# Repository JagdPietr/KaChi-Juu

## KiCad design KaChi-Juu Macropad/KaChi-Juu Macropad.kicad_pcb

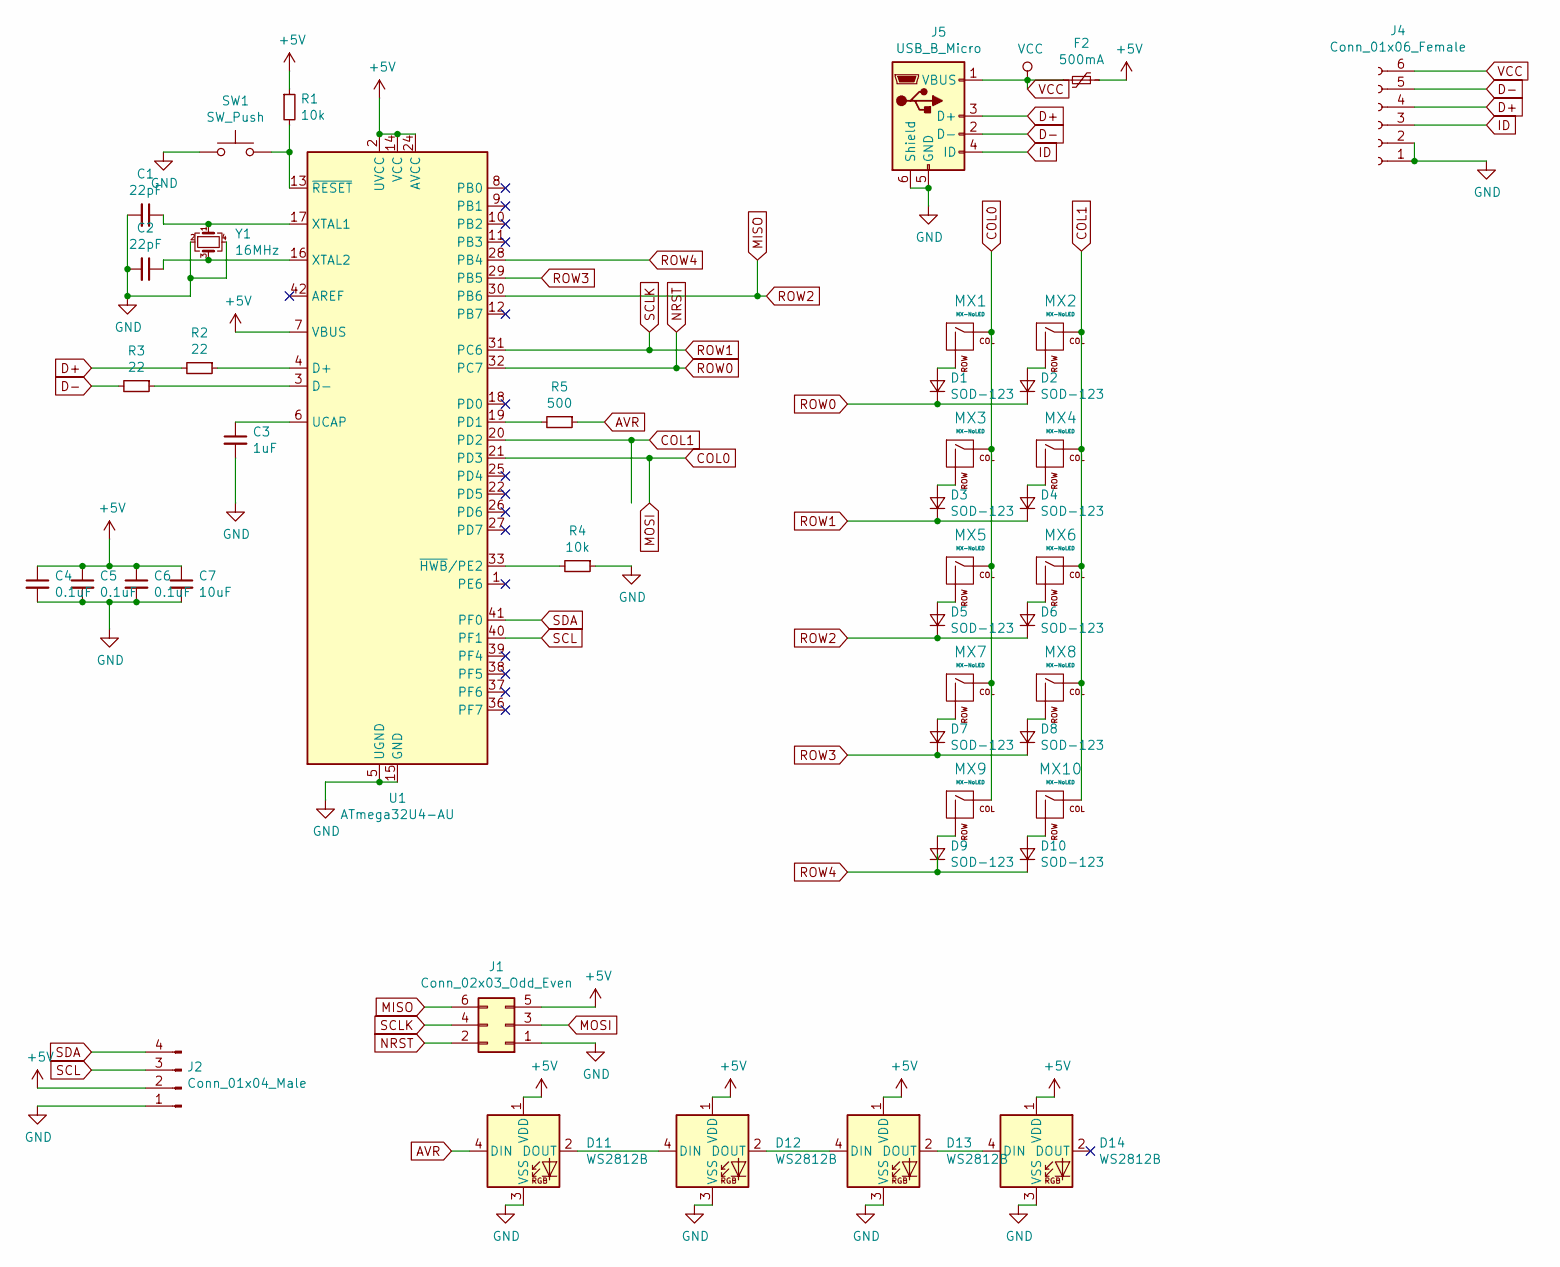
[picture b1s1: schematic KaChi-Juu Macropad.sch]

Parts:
C1, C2: 22pF; C_0805_2012Metric
C3: 1uF; C_0805_2012Metric
C4, C5, C6: 0.1uF; C_0805_2012Metric
C7: 10uF; C_0805_2012Metric
D1, D2, D3, D4, D5, D6, D7, D8, D9, D10: SOD-123; D_SOD-123
D11, D12, D13, D14: WS2812B; LED_WS2812B_PLCC4_5.0x5.0mm_P3.2mm
F2: 500mA; Fuse_1206_3216Metric
J1: Conn_02x03_Odd_Even; PinSocket_2x03_P2.54mm_Vertical
J2: Conn_01x04_Male; PinHeader_1x04_P2.54mm_Vertical
J4: Conn_01x06_Female; PinHeader_1x06_P2.54mm_Vertical
J5: USB_B_Micro; USB_Micro-B_Molex_47346-0001
MX1, MX2, MX3, MX4, MX5, MX6, MX7, MX8, MX9, MX10: MX-NoLED; MXOnly-1U-Hotswap
R1, R4: 10k; R_0805_2012Metric
R2, R3: 22; R_0805_2012Metric
R5: 500; R_0805_2012Metric
SW1: SW_Push; SKQG-1155865
U1: ATmega32U4-AU; TQFP-44_10x10mm_P0.8mm
Y1: 16MHz; Crystal_SMD_3225-4Pin_3.2x2.5mm

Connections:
+5V: C4.1, C5.1, C6.1, C7.1, D11.1 (VDD), D12.1 (VDD), D13.1 (VDD), D14.1 (VDD), F2.1, J1.5, J2.2, R1.1, U1.2 (UVCC), U1.7 (VBUS), U1.14 (VCC), U1.24 (AVCC), U1.34 (VCC), U1.44 (AVCC)
AVR: D11.4 (DIN), R5.1
COL0: J1.3, MX1.1 (COL), MX3.1 (COL), MX5.1 (COL), MX7.1 (COL), MX9.1 (COL), U1.21 (PD3)
COL1: MX2.1 (COL), MX4.1 (COL), MX6.1 (COL), MX8.1 (COL), MX10.1 (COL), U1.20 (PD2)
D+: J4.4, J5.3 (D+), R2.2
D-: J4.5, J5.2 (D-), R3.2
GND: C1.2, C2.2, C3.2, C4.2, C5.2, C6.2, C7.2, D11.3 (VSS), D12.3 (VSS), D13.3 (VSS), D14.3 (VSS), J1.1, J2.1, J4.1, J4.2, J5.5 (GND), J5.6 (Shield), R4.1, SW1.1, U1.5 (UGND), U1.15 (GND), U1.23 (GND), U1.35 (GND), U1.43 (GND), Y1.2, Y1.4
ID: J4.3, J5.4 (ID)
MISO: D5.1 (K), D6.1 (K), J1.6, U1.30 (PB6)
NRST: D1.1 (K), D2.1 (K), J1.2, U1.32 (PC7)
unnamed: C1.1, U1.17 (XTAL1), Y1.1
unnamed: C2.1, U1.16 (XTAL2), Y1.3
unnamed: C3.1, U1.6 (UCAP)
unnamed: D1.2 (A), MX1.2 (ROW)
unnamed: D2.2 (A), MX2.2 (ROW)
unnamed: D3.2 (A), MX3.2 (ROW)
unnamed: D4.2 (A), MX4.2 (ROW)
unnamed: D5.2 (A), MX5.2 (ROW)
unnamed: D6.2 (A), MX6.2 (ROW)
unnamed: D7.2 (A), MX7.2 (ROW)
unnamed: D8.2 (A), MX8.2 (ROW)
unnamed: D9.2 (A), MX9.2 (ROW)
unnamed: D10.2 (A), MX10.2 (ROW)
unnamed: D11.2 (DOUT), D12.4 (DIN)
unnamed: D12.2 (DOUT), D13.4 (DIN)
unnamed: D13.2 (DOUT), D14.4 (DIN)
unnamed: R1.2, SW1.2, U1.13 (~RESET)
unnamed: R2.1, U1.4 (D+)
unnamed: R3.1, U1.3 (D-)
unnamed: R4.2, U1.33 (~HWB~/PE2)
unnamed: R5.2, U1.19 (PD1)
ROW1: D3.1 (K), D4.1 (K), J1.4, U1.31 (PC6)
ROW3: D7.1 (K), D8.1 (K), U1.29 (PB5)
ROW4: D9.1 (K), D10.1 (K), U1.28 (PB4)
SCL: J2.3, U1.40 (PF1)
SDA: J2.4, U1.41 (PF0)
VCC: F2.2, J4.6, J5.1 (VBUS)

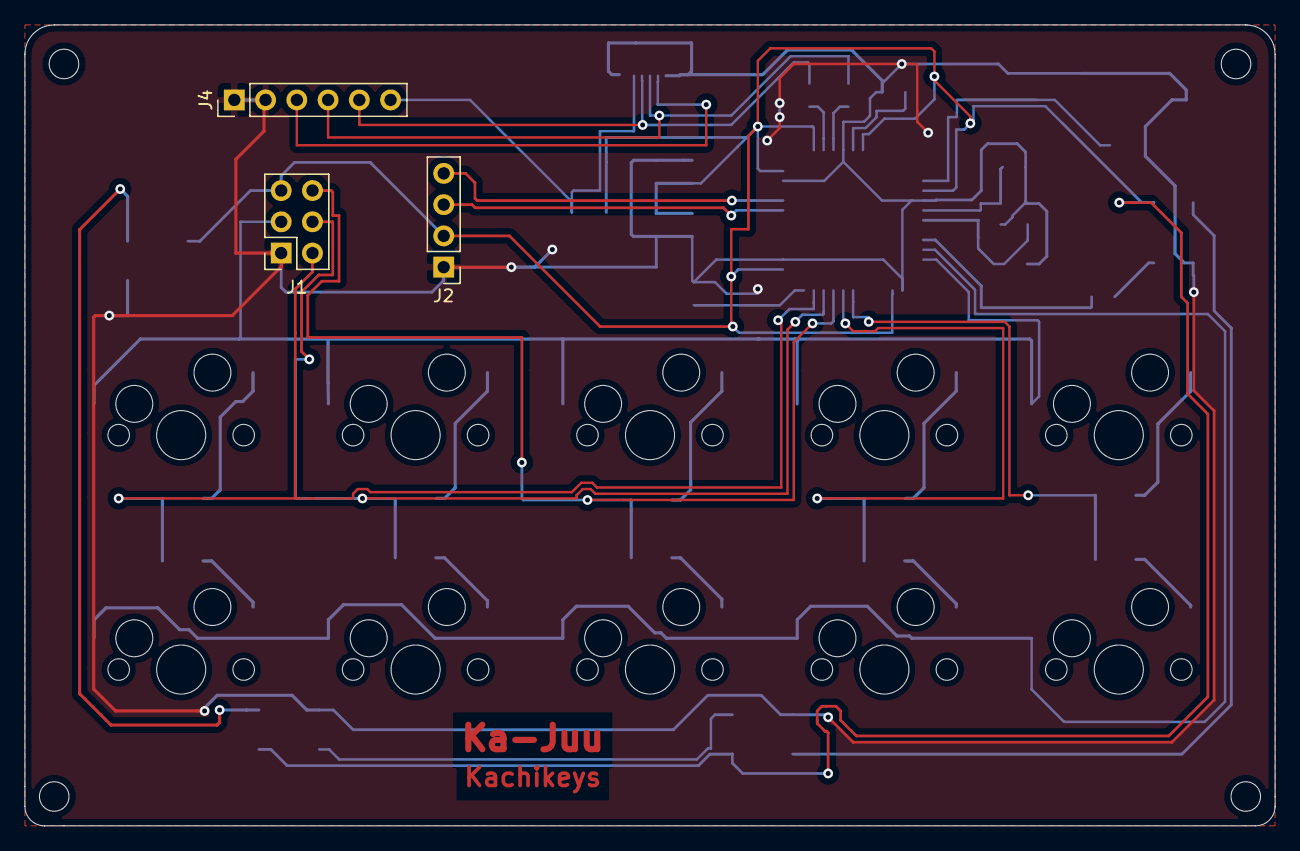
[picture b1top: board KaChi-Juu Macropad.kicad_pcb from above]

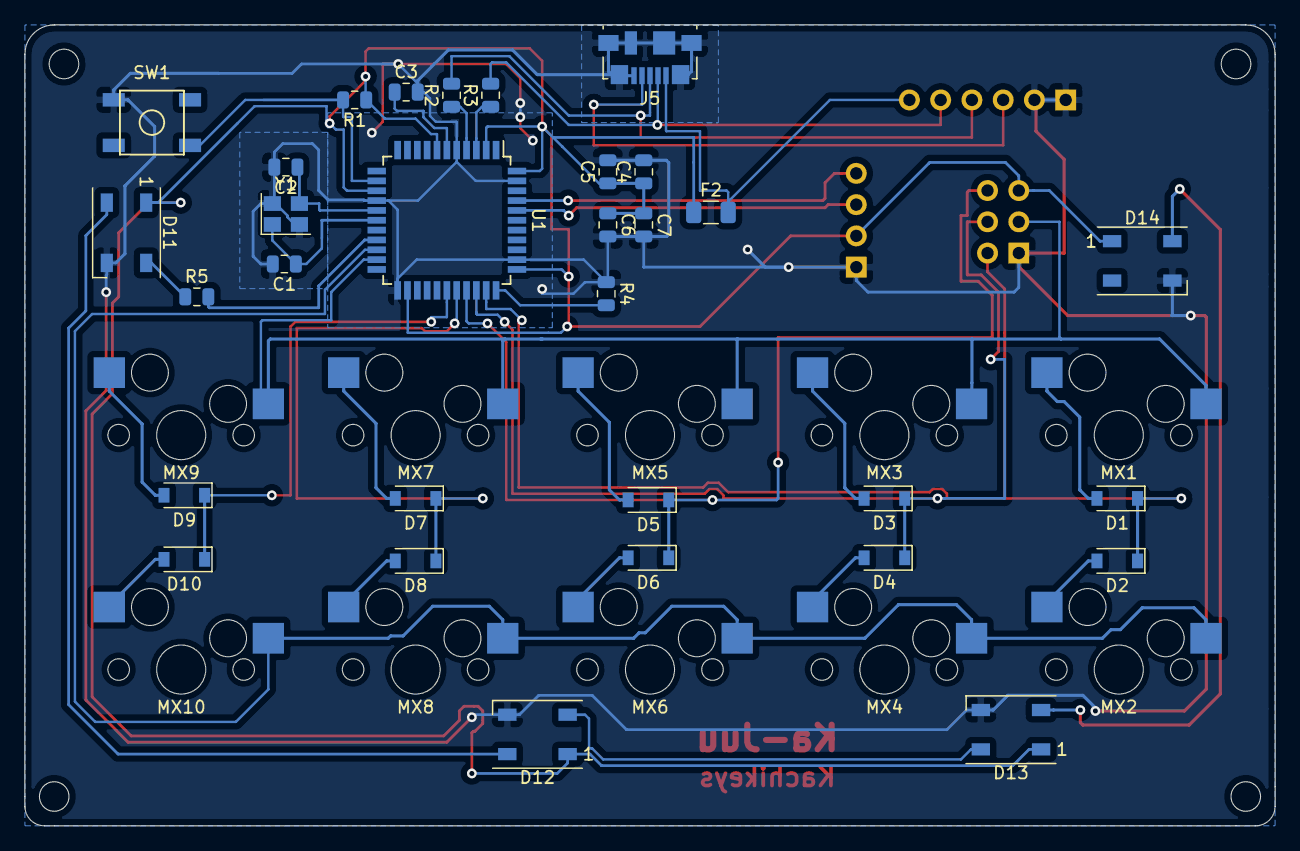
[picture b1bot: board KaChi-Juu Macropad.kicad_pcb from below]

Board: 2 copper layers, 101.6 x 65.1 mm, 44 parts (31 on the bottom side), 37 nets.

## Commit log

2020-04-04 Libraries Added
2020-04-04 Add submodules
2020-04-04 Schematics
2020-04-16 Updated PCB Routing
